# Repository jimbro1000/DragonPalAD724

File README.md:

# Dragon PAL Video Board Concept 3 #
This repository contains the design for
a video board for the Dragon 32 rev 3 
evolution main board

## YUV -> RGB ##
The design here converts the YUV output 
of the VDG chip into RGB in order to
drive an Analog Devices AD724JR 
signal modulator

Translation is performed per channel to calculate
the relative R-Y and B-Y values that can be 
combined with an inverted Y signal to produce
RGB. Each output channel can then be fine tuned for
strength independently.

The resulting RGB signals are fed to the
AD724 which provides signal modulation and
synthesizes the sync signals. The original
sync in the source luma signal is ignored.

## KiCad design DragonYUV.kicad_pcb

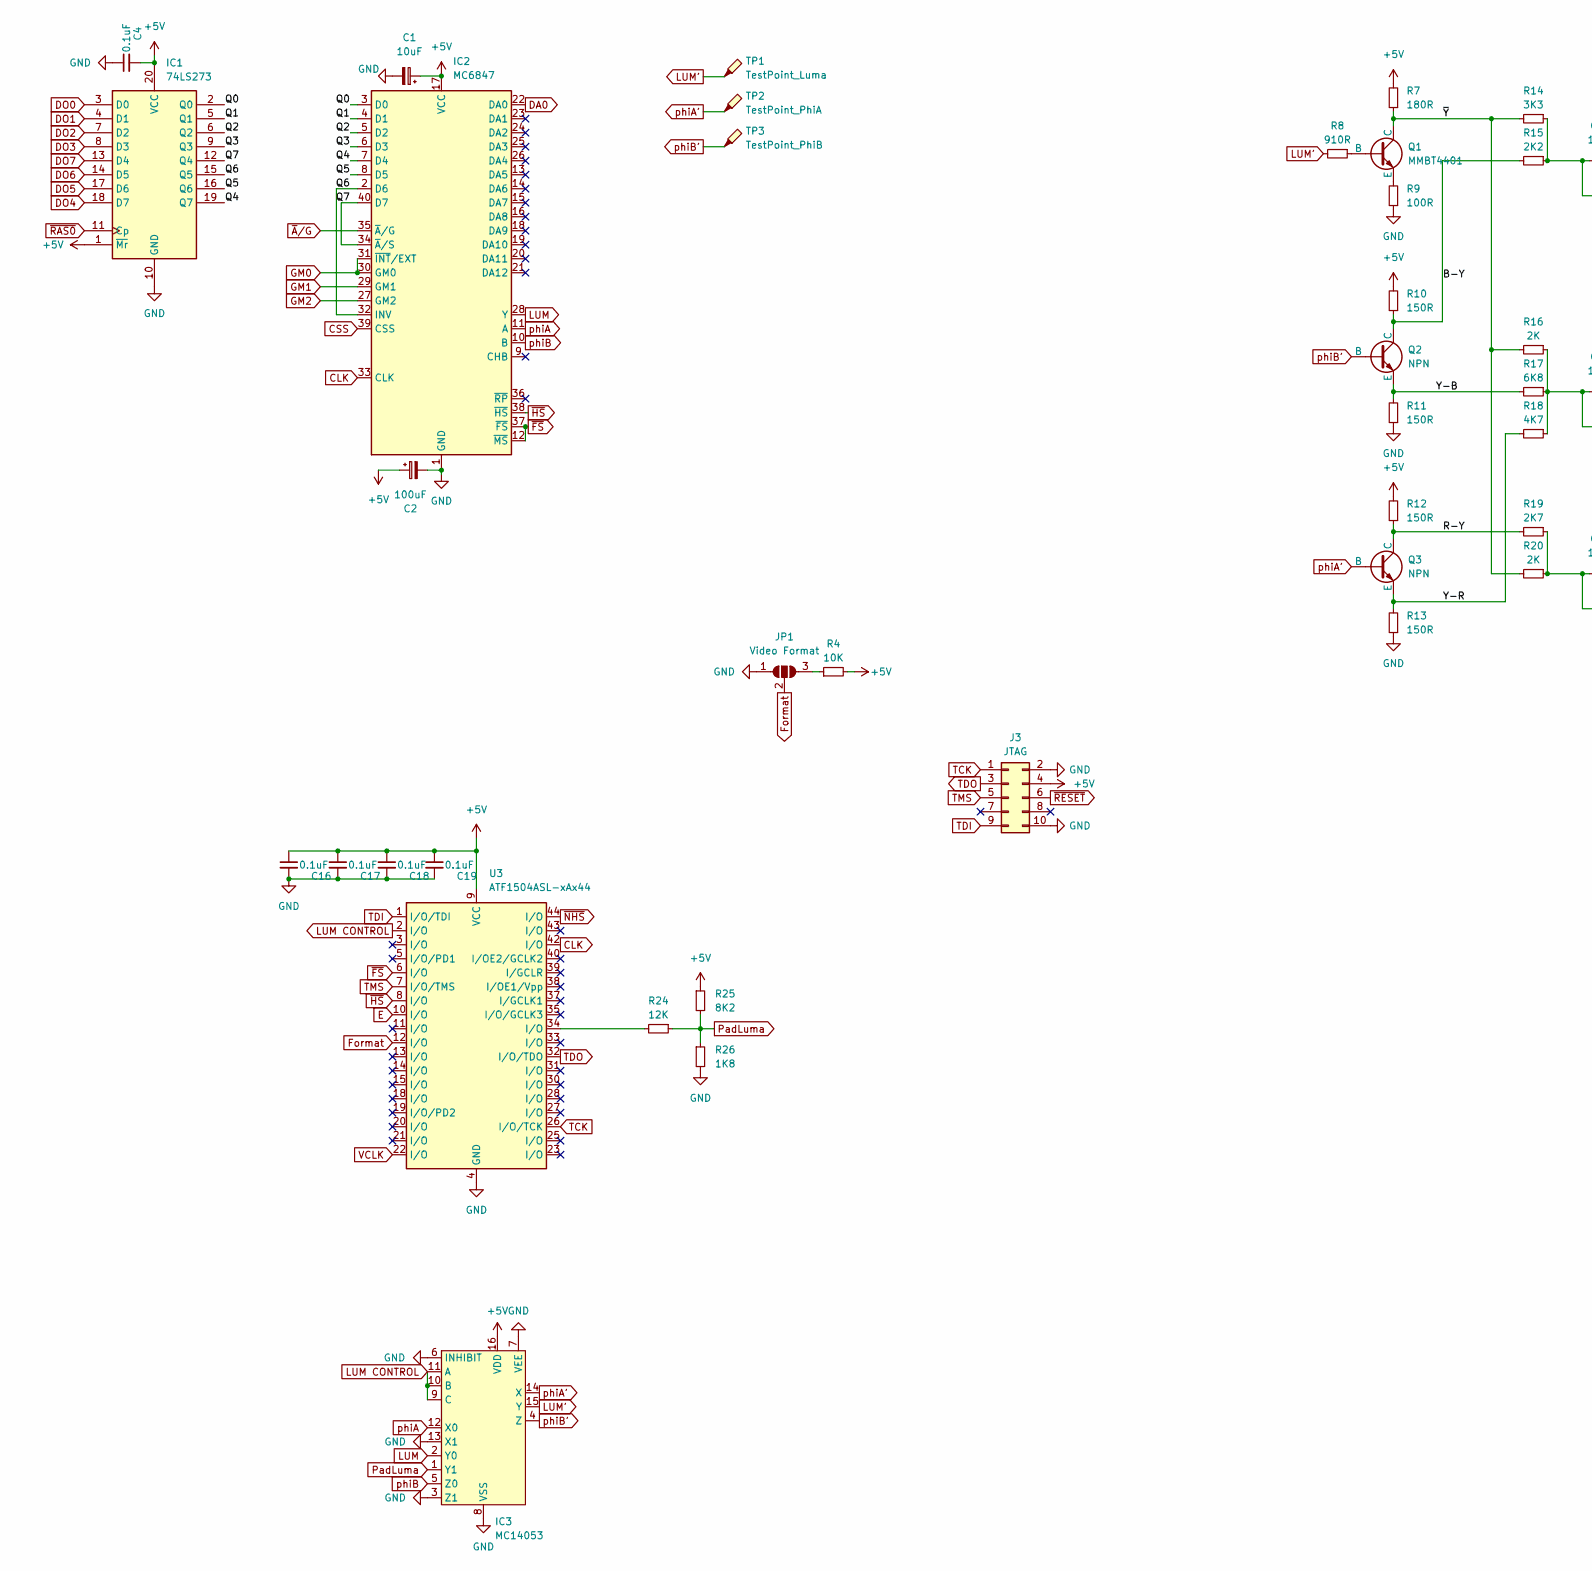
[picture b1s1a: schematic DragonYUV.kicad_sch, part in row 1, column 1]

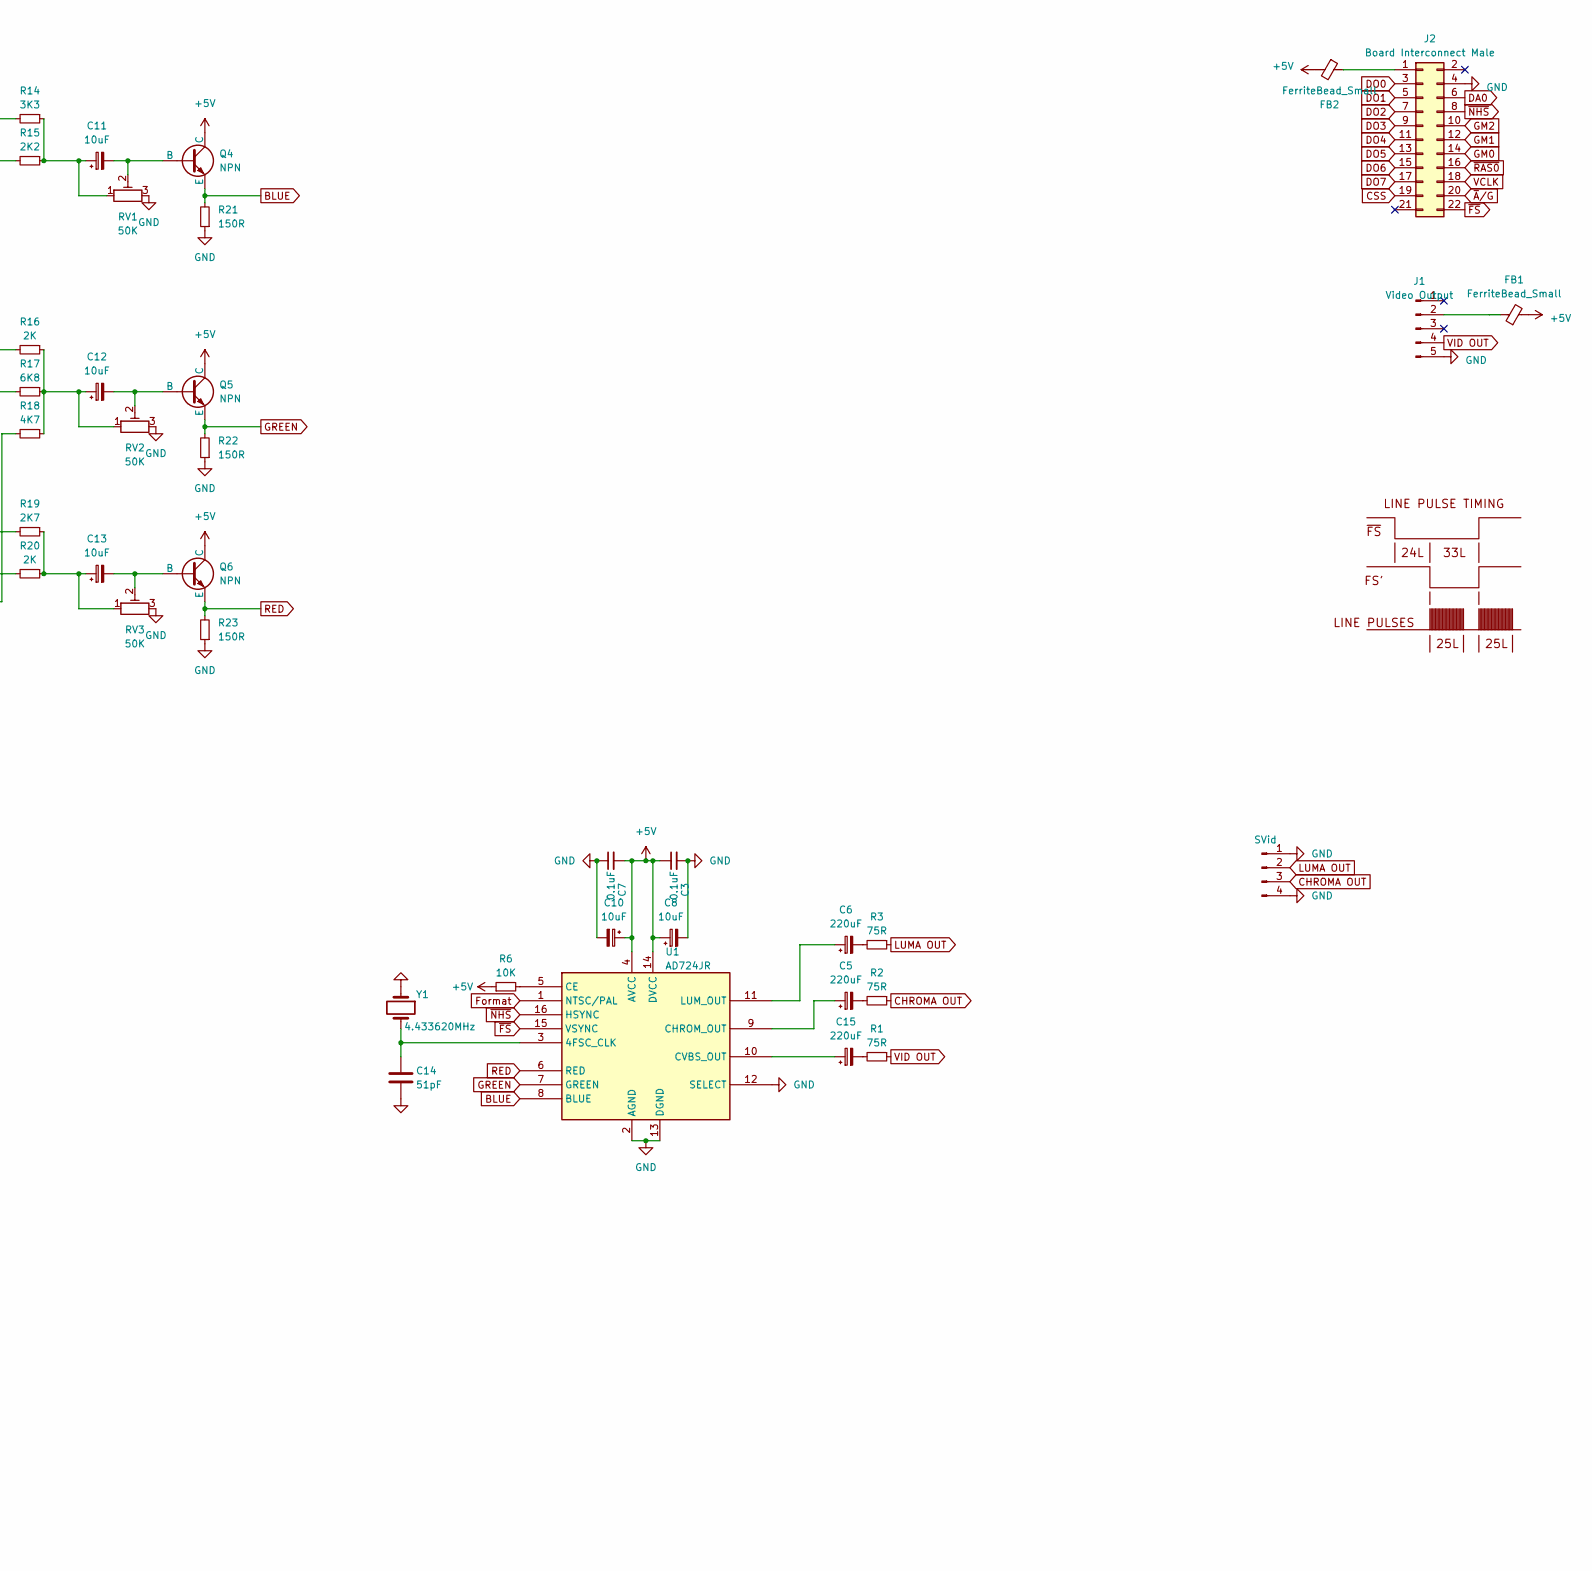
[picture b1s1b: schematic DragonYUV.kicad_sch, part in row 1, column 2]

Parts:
C1, C8, C10, C11, C12, C13: 10uF; CP_Elec_4x5.4; DigiKey 732-6401-1-ND
C2: 100uF; CP_Elec_6.3x5.8; DigiKey 732-8254-1-ND
C3, C4, C7, C16, C17, C18, C19: 0.1uF; C_0805_2012Metric_Pad1.18x1.45mm_HandSolder; DigiKey 399-C0805C104M5RAC7800CT-ND
C5, C6, C15: 220uF; CP_Elec_4x5.4; DigiKey 732-6401-1-ND
C14: 51pF; C_0805_2012Metric; DigiKey 399-C0805C510F1GAC7800CT-ND
FB1, FB2: FerriteBead_Small; L_0805_2012Metric_Pad1.15x1.40mm_HandSolder
IC1: 74LS273; SOIC-20W_7.5x12.8mm_P1.27mm; DigiKey 296-3682-1-ND
IC2: MC6847; DIP-40_W15.24mm
IC3: MC14053; SOIC-16_3.9x9.9mm_P1.27mm; DigiKey 296-2059-ND
J1: Video Output; PinHeader_1x05_P2.54mm_Vertical
J2: Board Interconnect Male; PinHeader_2x11_P2.54mm_Vertical
J3: JTAG; PinHeader_2x05_P2.54mm_Vertical
J4: SVid; PinHeader_1x04_P2.54mm_Vertical
JP1: Video Format; SolderJumper-3_P1.3mm_Open_Pad1.0x1.5mm_NumberLabels
Q1: MMBT4401; SOT-23-3
Q2, Q3, Q4, Q5, Q6: NPN; SOT-23-3
R1, R2, R3: 75R; R_0805_2012Metric_Pad1.20x1.40mm_HandSolder; DigiKey CF14JT6K80CT-ND
R4, R6: 10K; R_0805_2012Metric_Pad1.20x1.40mm_HandSolder; DigiKey CF14JT6K80CT-ND
R7: 180R; R_0805_2012Metric_Pad1.20x1.40mm_HandSolder; DigiKey CF14JT6K80CT-ND
R8: 910R; R_0805_2012Metric_Pad1.20x1.40mm_HandSolder; DigiKey CF14JT6K80CT-ND
R9: 100R; R_0805_2012Metric_Pad1.20x1.40mm_HandSolder; DigiKey CF14JT6K80CT-ND
R10, R11, R12, R13: 150R; R_0805_2012Metric_Pad1.20x1.40mm_HandSolder; DigiKey CF14JT6K80CT-ND
R14: 3K3; R_0805_2012Metric_Pad1.20x1.40mm_HandSolder; DigiKey CF14JT6K80CT-ND
R15: 2K2; R_0805_2012Metric_Pad1.20x1.40mm_HandSolder; DigiKey CF14JT6K80CT-ND
R16, R20: 2K; R_0805_2012Metric_Pad1.20x1.40mm_HandSolder; DigiKey CF14JT6K80CT-ND
R17: 6K8; R_0805_2012Metric_Pad1.20x1.40mm_HandSolder; DigiKey CF14JT6K80CT-ND
R18: 4K7; R_0805_2012Metric_Pad1.20x1.40mm_HandSolder; DigiKey CF14JT6K80CT-ND
R19: 2K7; R_0805_2012Metric_Pad1.20x1.40mm_HandSolder; DigiKey CF14JT6K80CT-ND
R21, R22, R23: 150R; R_0603_1608Metric; DigiKey CF14JT6K80CT-ND
R24: 12K; R_0805_2012Metric_Pad1.20x1.40mm_HandSolder; DigiKey CF14JT6K80CT-ND
R25: 8K2; R_0805_2012Metric_Pad1.20x1.40mm_HandSolder; DigiKey CF14JT6K80CT-ND
R26: 1K8; R_0805_2012Metric_Pad1.20x1.40mm_HandSolder; DigiKey CF14JT6K80CT-ND
RV1, RV2, RV3: 50K; Potentiometer_Bourns_TC33X_Vertical; DigiKey TC42X-2-503ECT-ND
TP1: TestPoint_Luma; TestPoint_Pad_D1.0mm
TP2: TestPoint_PhiA; TestPoint_Pad_D1.0mm
TP3: TestPoint_PhiB; TestPoint_Pad_D1.0mm
U1: AD724JR; SOIC-16W_7.5x10.3mm_P1.27mm
U3: ATF1504ASL-xAx44; TQFP-44_10x10mm_P0.8mm; DigiKey ATF1504ASL-25AU44-ND
Y1: 4.433620MHz; Crystal_HC18-U_Vertical; DigiKey XC1263CT-ND
Z1: LINE_PULSE_DIAGRAM

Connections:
+5V: C1.1, C2.1, C3.1, C4.2, C7.2, C8.1, C10.1, C16.1, C17.1, C18.1, C19.1, FB1.2, FB2.2, IC1.1 (~Mr), IC1.20 (VCC), IC2.17 (VCC), IC3.16 (VDD), J3.4, Q4.1 (C), Q5.1 (C), Q6.1 (C), R4.2, R6.1, R7.2, R10.2, R12.2, R25.1, U1.4 (AVCC), U1.14 (DVCC), U3.9 (VCC), U3.17 (VCC), U3.29 (VCC), U3.41 (VCC)
/B-Y: Q2.1 (C), R10.1, R15.2
/Q0: IC1.2 (Q0), IC2.3 (D0)
/Q1: IC1.5 (Q1), IC2.4 (D1)
/Q2: IC1.6 (Q2), IC2.5 (D2)
/Q3: IC1.9 (Q3), IC2.6 (D3)
/Q4: IC1.19 (Q7), IC2.7 (D4)
/Q5: IC1.16 (Q6), IC2.8 (D5)
/Q6: IC1.15 (Q5), IC2.2 (D6), IC2.32 (INV)
/Q7: IC1.12 (Q4), IC2.34 (~A/S), IC2.40 (D7)
/R-Y: Q3.1 (C), R12.1, R19.2
/Y-B: Q2.3 (E), R11.2, R17.2
/Y-R: Q3.3 (E), R13.2, R18.2
/~Y: Q1.1 (C), R7.1, R14.2, R16.2, R20.2
BLUE: Q4.3 (E), R21.2, U1.8 (BLUE)
CHROMA OUT: J4.3, R2.1
CLK: IC2.33 (CLK), U3.42 (I/O)
CSS: IC2.39 (CSS), J2.19
DA0: IC2.22 (DA0), J2.6
DO0: IC1.3 (D0), J2.3
DO1: IC1.4 (D1), J2.5
DO2: IC1.7 (D2), J2.7
DO3: IC1.8 (D3), J2.9
DO4: IC1.18 (D7), J2.11
DO5: IC1.17 (D6), J2.13
DO6: IC1.14 (D5), J2.15
DO7: IC1.13 (D4), J2.17
E: U3.10 (I/O)
Format: JP1.2 (C), U1.1 (NTSC/PAL), U3.12 (I/O)
GM0: IC2.30 (GM0), IC2.31 (~INT/EXT), J2.14
GM1: IC2.29 (GM1), J2.12
GM2: IC2.27 (GM2), J2.10
GND: C1.2, C2.2, C3.2, C4.1, C7.1, C8.2, C10.2, C14.2, C16.2, C17.2, C18.2, C19.2, IC1.10 (GND), IC2.1 (GND), IC3.3 (Z1), IC3.6 (INHIBIT), IC3.7 (VEE), IC3.8 (VSS), IC3.13 (X1), J1.5, J2.4, J3.2, J3.10, J4.1, J4.4, JP1.1 (A), R9.1, R11.1, R13.1, R21.1, R22.1, R23.1, R26.2, RV1.3, RV2.3, RV3.3, U1.2 (AGND), U1.12 (SELECT), U1.13 (DGND), U3.4 (GND), U3.16 (GND), U3.24 (GND), U3.36 (GND), Y1.1
GREEN: Q5.3 (E), R22.2, U1.7 (GREEN)
LUM: IC2.28 (Y), IC3.2 (Y0)
LUM CONTROL: IC3.9 (C), IC3.10 (B), IC3.11 (A), U3.2 (I/O)
LUM': IC3.15 (Y), R8.2, TP1.1
LUMA OUT: J4.2, R3.1
unnamed: C5.2, R2.2
unnamed: C6.2, R3.2
unnamed: C11.1, R14.1, R15.1, RV1.1
unnamed: C12.1, R16.1, R17.1, R18.1, RV2.1
unnamed: C13.1, R19.1, R20.1, RV3.1
unnamed: C15.2, R1.2
unnamed: FB1.1, J1.2
unnamed: FB2.1, J2.1
unnamed: JP1.3 (B), R4.1
unnamed: Q1.2 (B), R8.1
unnamed: Q1.3 (E), R9.2
unnamed: C11.2, Q4.2 (B), RV1.2
unnamed: C12.2, Q5.2 (B), RV2.2
unnamed: C13.2, Q6.2 (B), RV3.2
unnamed: R24.2, U3.34 (I/O)
unnamed: C14.1, U1.3 (4FSC_CLK), Y1.2
unnamed: R6.2, U1.5 (CE)
unnamed: C5.1, U1.9 (CHROM_OUT)
unnamed: C15.1, U1.10 (CVBS_OUT)
unnamed: C6.1, U1.11 (LUM_OUT)
PadLuma: IC3.1 (Y1), R24.1, R25.2, R26.1
RED: Q6.3 (E), R23.2, U1.6 (RED)
TCK: J3.1, U3.26 (I/O/TCK)
TDI: J3.9, U3.1 (I/O/TDI)
TDO: J3.3, U3.32 (I/O/TDO)
TMS: J3.5, U3.7 (I/O/TMS)
VCLK: J2.18, U3.22 (I/O)
VID OUT: J1.4, R1.1
phiA: IC2.11 (A), IC3.12 (X0)
phiA': IC3.14 (X), Q3.2 (B), TP2.1
phiB: IC2.10 (B), IC3.5 (Z0)
phiB': IC3.4 (Z), Q2.2 (B), TP3.1
~A/G: IC2.35 (~A/G), J2.20
~FS: IC2.12 (~MS), IC2.37 (~FS), J2.22, U1.15 (VSYNC), U3.6 (I/O)
~HS: IC2.38 (~HS), U3.8 (I/O)
~NHS: J2.8, U1.16 (HSYNC), U3.44 (I/O)
~RAS0: IC1.11 (Cp), J2.16
~RESET: J3.6

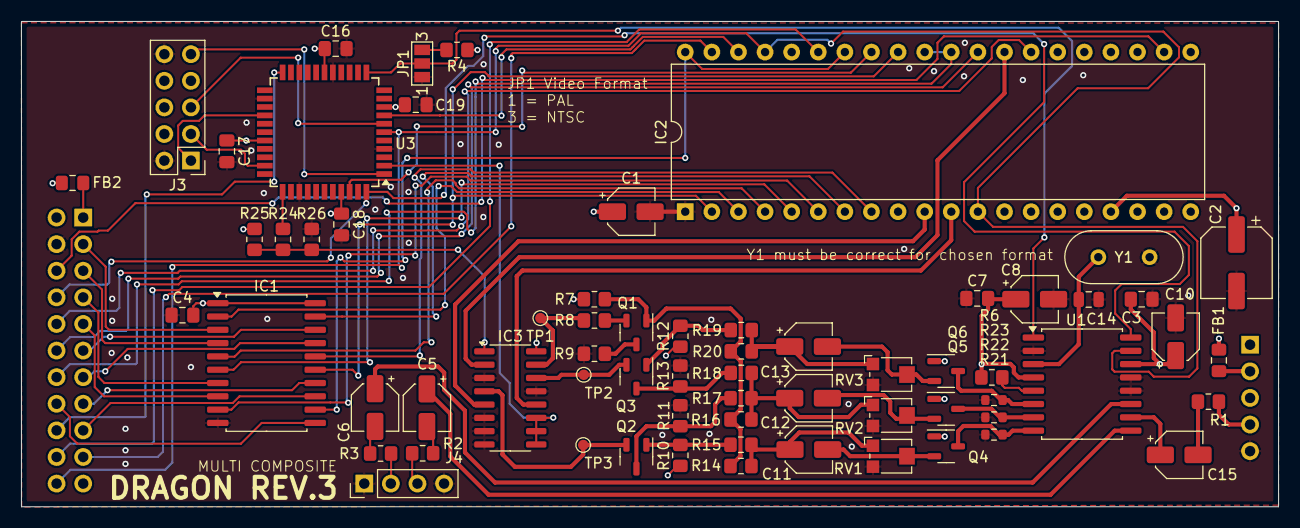
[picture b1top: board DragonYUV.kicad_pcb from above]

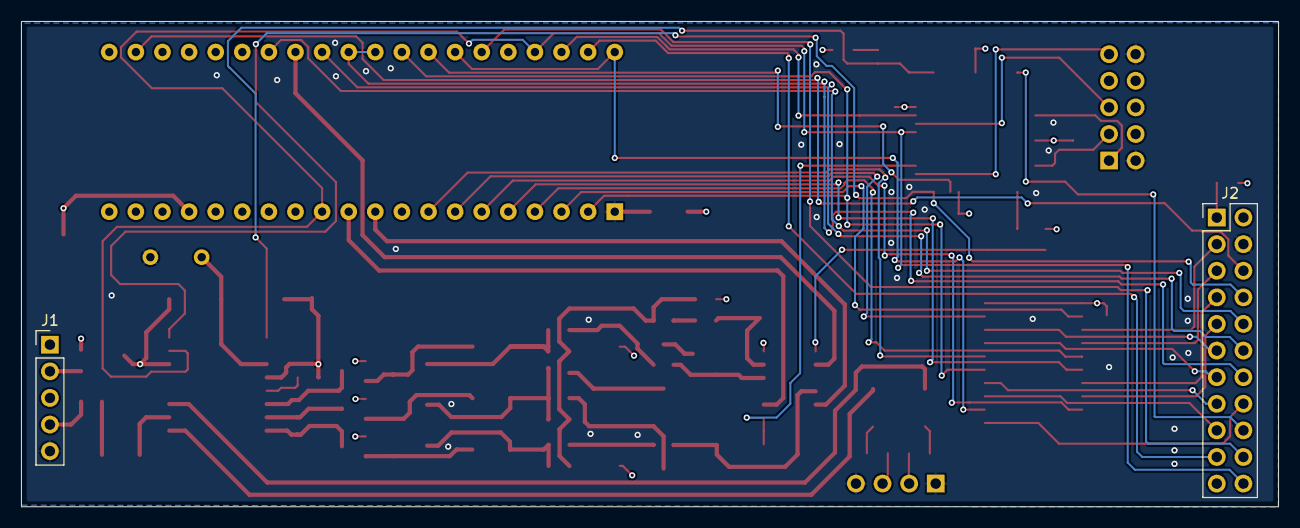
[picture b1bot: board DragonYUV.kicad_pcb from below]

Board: 4 copper layers, 120.0 x 46.3 mm, 68 parts (2 on the bottom side), 74 nets.

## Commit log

2024-05-02 tidy up
2024-05-03 update pcb file
2024-05-03 reworked layout
2024-05-03 Clean up board Improve trace quality
2024-06-12 bolster video output routing
2024-06-12 convert to cpld
2025-02-11 update design to provide ntsc and pal switching
2025-02-12 rework schematics for demux of video
2025-02-16 compose verilog
